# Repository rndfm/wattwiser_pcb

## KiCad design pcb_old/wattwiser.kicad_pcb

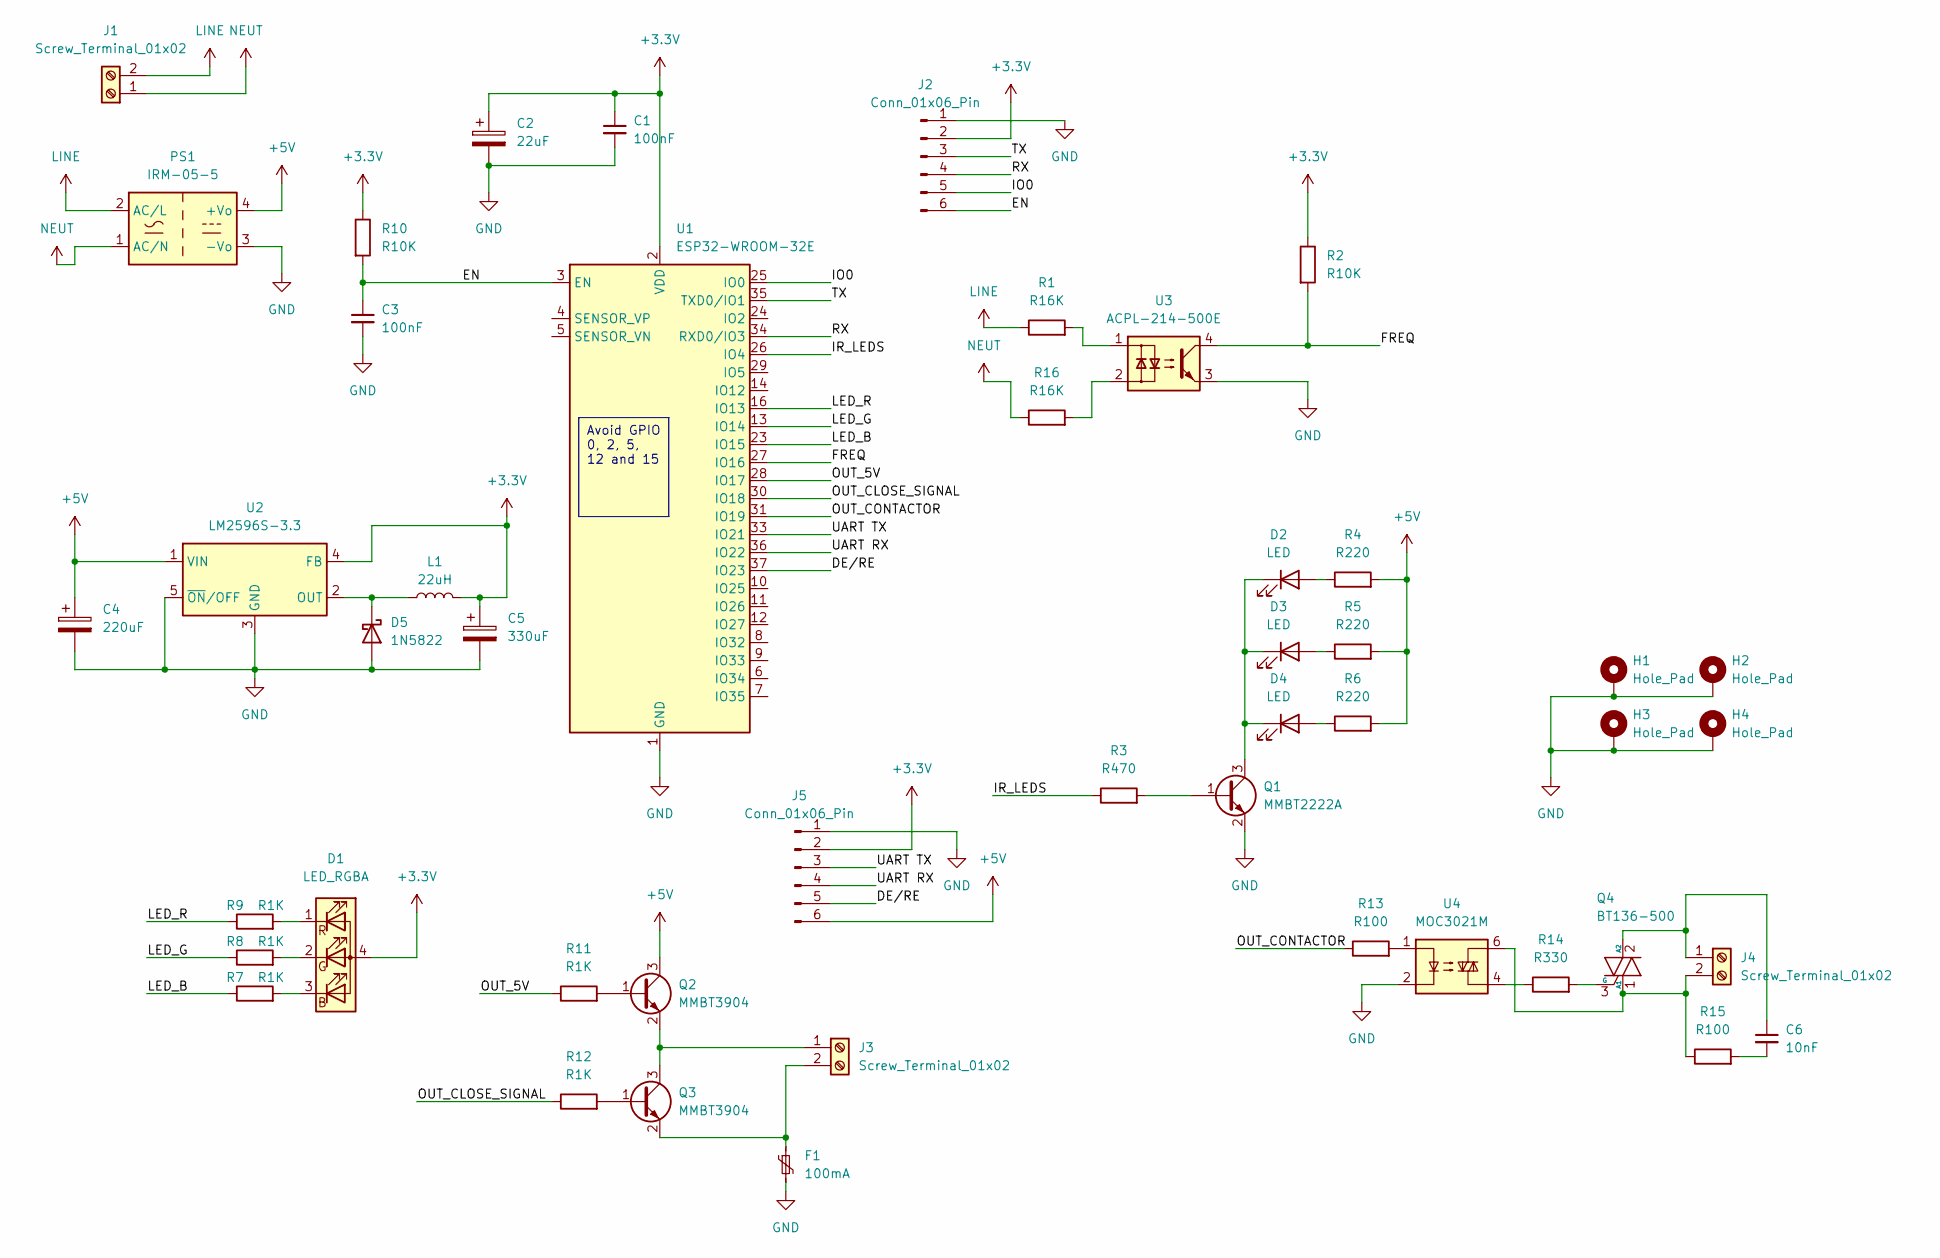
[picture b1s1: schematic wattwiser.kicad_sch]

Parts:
C1, C3: 100nF; C_0402_1005Metric_Pad0.74x0.62mm_HandSolder
C2: 22uF; C_1206_3216Metric_Pad1.33x1.80mm_HandSolder
C4: 220uF; CP_Radial_D10.0mm_P5.00mm
C5: 330uF; CP_Radial_D10.0mm_P5.00mm
C6: 10nF; C_0402_1005Metric_Pad0.74x0.62mm_HandSolder
D1: LED_RGBA; LED_RGB_Wuerth-PLCC4_3.2x2.8mm_150141M173100
D2, D3, D4: LED; LED_D5.0mm
D5: 1N5822; D_DO-201AD_P15.24mm_Horizontal
F1: 100mA; Fuse_1206_3216Metric_Pad1.42x1.75mm_HandSolder
H1, H2, H3, H4: Hole_Pad; MountingHole_3.2mm_M3_Pad_Via
J1, J3, J4: Screw_Terminal_01x02; TerminalBlock_Phoenix_MKDS-1,5-2_1x02_P5.00mm_Horizontal
J2, J5: Conn_01x06_Pin; PinSocket_1x06_P2.54mm_Vertical
L1: 22uH; L_Abracon_ASPI-4030S
PS1: IRM-05-5; Converter_ACDC_MeanWell_IRM-05-xx_THT
Q1: MMBT2222A; SOT-23
Q2, Q3: MMBT3904; SOT-23
Q4: BT136-500; TO-220-3_Vertical
R1, R16: R16K; R_2512_6332Metric_Pad1.40x3.35mm_HandSolder
R2, R10: R10K; R_0402_1005Metric_Pad0.72x0.64mm_HandSolder
R3: R470; R_0402_1005Metric_Pad0.72x0.64mm_HandSolder
R4, R5, R6: R220; R_0402_1005Metric_Pad0.72x0.64mm_HandSolder
R7, R8, R9, R11, R12: R1K; R_0402_1005Metric_Pad0.72x0.64mm_HandSolder
R13, R15: R100; R_0402_1005Metric_Pad0.72x0.64mm_HandSolder
R14: R330; R_0402_1005Metric_Pad0.72x0.64mm_HandSolder
U1: ESP32-WROOM-32E
U2: LM2596S-3.3; TO-263-5_TabPin3
U3: ACPL-214-500E; SOP-4_4.4x2.6mm_P1.27mm
U4: MOC3021M; DIP-6_W7.62mm

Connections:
+3.3V: C1.1, C2.1, C5.1, D1.4 (A), J2.2, J5.2, L1.2, R2.1, R10.1, U1.2 (VDD), U2.4 (FB)
+5V: C4.1, J5.6, PS1.4 (+Vo), Q2.3 (C), R4.2, R5.2, R6.2, U2.1 (VIN)
/DE/RE: J5.5, U1.37 (IO23)
/EN: C3.1, J2.6, R10.2, U1.3 (EN)
/FREQ: R2.2, U1.27 (IO16), U3.4
/IO0: J2.5, U1.25 (IO0)
/IR_LEDS: R3.1, U1.26 (IO4)
/LED_B: R7.1, U1.23 (IO15)
/LED_G: R8.1, U1.13 (IO14)
/LED_R: R9.1, U1.16 (IO13)
/OUT_5V: R11.1, U1.28 (IO17)
/OUT_CLOSE_SIGNAL: R12.1, U1.30 (IO18)
/OUT_CONTACTOR: R13.1, U1.31 (IO19)
/RX: J2.4, U1.34 (RXD0/IO3)
/TX: J2.3, U1.35 (TXD0/IO1)
/UART RX: J5.4, U1.36 (IO22)
/UART TX: J5.3, U1.33 (IO21)
GND: C1.2, C2.2, C3.2, C4.2, C5.2, D5.2 (A), F1.2, H1.1, H2.1, H3.1, H4.1, J2.1, J5.1, PS1.3 (-Vo), Q1.2 (E), U1.1 (GND), U1.15 (GND), U1.38 (GND), U1.39 (GND), U2.3 (GND), U2.5 (~ON/OFF), U3.3, U4.2
LINE: J1.2, PS1.2 (AC/L), R1.1
NEUT: J1.1, PS1.1 (AC/N), R16.1
unnamed: C6.2, R15.2
unnamed: D1.3 (BK), R7.2
unnamed: D1.2 (GK), R8.2
unnamed: D1.1 (RK), R9.2
unnamed: D2.2 (A), R4.1
unnamed: D2.1 (K), D3.1 (K), D4.1 (K), Q1.3 (C)
unnamed: D3.2 (A), R5.1
unnamed: D4.2 (A), R6.1
unnamed: D5.1 (K), L1.1, U2.2 (OUT)
unnamed: J3.1, Q2.2 (E), Q3.3 (C)
unnamed: F1.1, J3.2, Q3.2 (E)
unnamed: C6.1, J4.1, Q4.2 (A2)
unnamed: J4.2, Q4.1 (A1), R15.1, U4.6
unnamed: Q1.1 (B), R3.2
unnamed: Q2.1 (B), R11.2
unnamed: Q3.1 (B), R12.2
unnamed: Q4.3 (G), R14.2
unnamed: R1.2, U3.1
unnamed: R13.2, U4.1
unnamed: R14.1, U4.4
unnamed: R16.2, U3.2

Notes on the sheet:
Avoid GPIO 0, 2, 5, 12 and 15

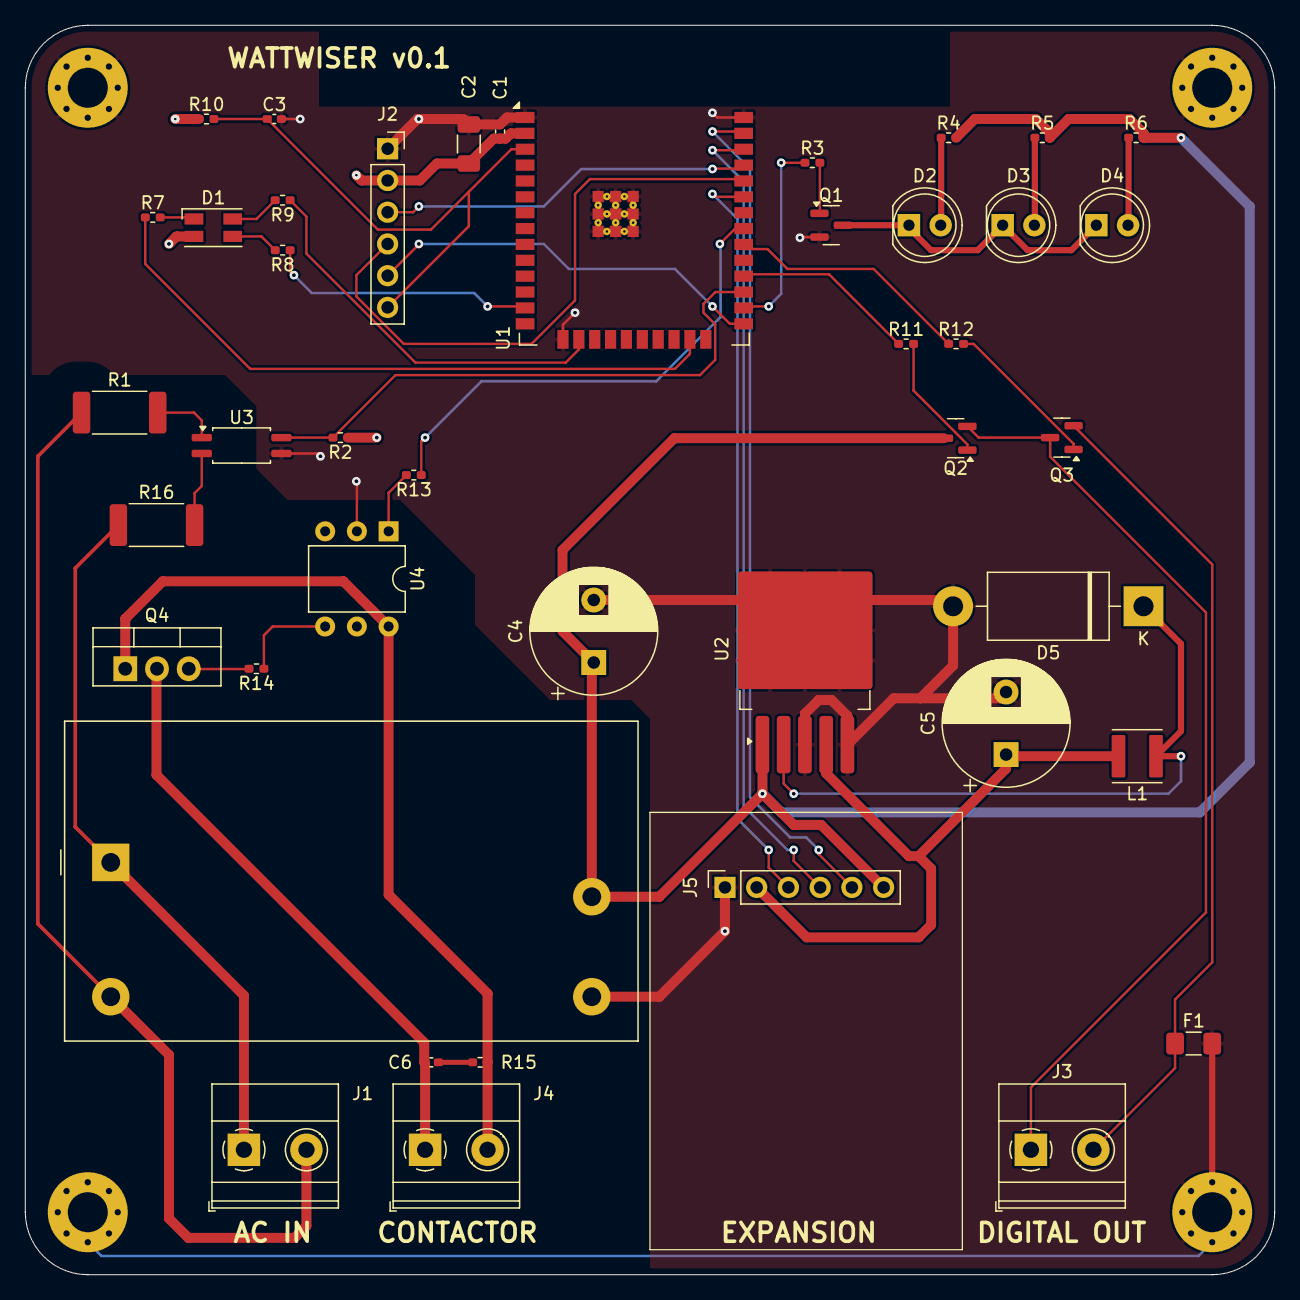
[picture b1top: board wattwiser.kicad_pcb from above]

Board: 4 copper layers, 100.0 x 100.0 mm, 47 parts (0 on the bottom side), 41 nets.

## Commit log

2024-07-09 initial
2024-07-09 Add .whitesource configuration file
2024-07-09 Add old pcb
